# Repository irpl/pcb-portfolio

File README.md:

# PCB Design Portfolio

A selection of custom printed circuit boards I have designed and built, presented newest first. Each board was designed to solve a specific problem — a teaching platform, a weather station, and a remote water-quality monitor — rather than as a design exercise, and each one was fabricated and brought up in hardware.

---

## 1. ESP32 Sensor & Power Control Board

*Designed for the IoT course I teach at UWI.*

**Design files:** [KiCad schematic, layout, and project files →](https://github.com/irpl/ecse-simple-smart-hub-project-circuit)

This is the coursework platform board for the Internet of Things course I teach. It gives students a single board that covers the full loop of an IoT system: read the physical world, talk to a server, and act on the physical world in response.

An onboard **ESP32** reads a temperature sensor and a PIR motion sensor, and reports to a remote server. The server decides what should happen and instructs the ESP32, which then switches power through one of two **MOSFETs** to the corresponding output terminal. In other words, incoming power is routed to either of two loads under remote control — the two outputs are silkscreened `FAN` and `LIGHT`, which is the scenario students work through.

**Design notes**
- A landing footprint for an off-the-shelf **4.5–28 V** buck module (`J6`), so the board runs from any plain barrel-jack supply without designing a regulator onto it.
- Two low-side MOSFET switches (**IRLZ44N**, TO-220), each with a gate resistor. Logic-level parts were chosen deliberately: a standard MOSFET like the IRF-series needs several volts more than an ESP32's 3.3 V GPIO can supply to fully turn on, and would run hot in partial conduction. The IRLZ44N is fully enhanced from logic-level drive, so the ESP32 can switch real loads directly with no gate driver.
- Screw terminals for `TEMP`, `FAN` and `LIGHT`, a barrel jack for `POWER IN`, and a 3-pin header for the `PIR` — so students can wire and rewire the board without soldering.

The bare board and two populated builds are shown below — one with the ESP32 devkit soldered directly, and one built with female headers and a drop-in buck module so the ESP32 can be swapped out. Making the board survive a classroom full of students was as much a design constraint as the circuit itself.

<table>
  <tr>
    <th>Bare board</th>
    <th colspan="2">Assembled board</th>
  </tr>
  <tr>
    <td></td>
    <td></td>
    <td></td>
  </tr>
  <tr>
    <td></td>
    <td align="center"><sub>ESP32 soldered directly</sub></td>
    <td align="center"><sub>ESP32 on removable headers</sub></td>
  </tr>
</table>

---

## 2. Raspberry Pi Zero Weather Station HAT

**Design files:** [fab-ready Gerbers, plus a schematic and layout reconstructed from the copper →](https://github.com/irpl/pi-zero-weather-hat-circuit) &nbsp;•&nbsp; **Firmware:** [pi-weather →](https://github.com/irpl/pi-weather)

A custom HAT for the Raspberry Pi Zero, built to drive a weather station kit I had bought a few years earlier. Rather than leave the circuit on a breadboard or commit it to perfboard, I designed a proper HAT for it.

I started from a basic Pi Zero HAT footprint found on GitHub, which gave me only the board outline, the four mounting holes, and the GPIO header. **Everything else on the board is my own design.**

**Design notes**
- A footprint for a **BME280** breakout provides temperature and humidity (not fitted in the photos below).
- An **MCP3008** ADC reads the kit's resistive wind vane, since the Pi has no analogue inputs of its own.
- Two **RJ11/RJ12 jacks** bring in the kit's wind and rainfall sensors — silkscreened `Wind` and `RainFall` — so the outdoor sensors plug in with standard cable instead of flying leads.
- Sized and drilled to sit on the Pi Zero as a proper HAT, so the finished unit stays compact enough to deploy.

Laid out in **KiCad** as a two-layer board and fabricated in November 2020. The [design files](https://github.com/irpl/pi-zero-weather-hat-circuit) include the exact Gerber and drill set sent to the fab, so the board is reproducible as-is.

The original KiCad project for this board was lost. The schematic and layout in that repo were **reconstructed from the Gerbers** — the netlist recovered from the copper itself, then cross-checked against the firmware — and are clearly labelled as such.

| Bare boards (fab batch) | Assembled, seated on a Pi Zero | HAT and Pi Zero (exploded) |
|---|---|---|
|  |  |  |

---

## 3. Water Quality Sensor Interface Board

**Design files:** [Eagle schematic and layout →](https://github.com/irpl/water-quality-sensor-circuit) &nbsp;•&nbsp; **Server:** [watermon — the listener this board uploads to →](https://github.com/irpl/watermon)

The oldest board here, built to get readings off a water quality sensor and onto a server with no wired network anywhere nearby.

The sensor speaks **RS-232**, which a microcontroller cannot read directly. On this board an **Arduino Nano** sits behind a **MAX233** transceiver that converts the sensor's incoming RS-232 signals down to TTL serial the Nano can read. The Nano then pushes that data to a remote server over the cellular network using a **SIM800** module with an ordinary SIM and data plan.

**Design notes**
- **MAX233** rather than the more common MAX232: it integrates the charge-pump capacitors, so the RS-232 level shifter needs no external capacitors at all — fewer parts to place and fewer things to fail in the field.
- **DB9 connector** on the board edge so the sensor plugs straight in with a standard serial cable.
- Footprints for the Arduino Nano and the Adafruit **SIM800** cellular module, plus a 2×3 ICSP header.
- Screw terminal for field power.

This one is essentially a protocol-and-transport bridge: a legacy serial instrument on one end, a cellular uplink on the other, and level translation in between.

The board was laid out in **Eagle** as a two-layer design; the [schematic and layout](https://github.com/irpl/water-quality-sensor-circuit) are available separately.

| Bare board | Assembled |
|---|---|
|  |  |

---

## About

These boards span roughly seven years of design work, from the RS-232-to-cellular bridge through to the current teaching platform. Across all three the common thread is designing boards to be **built, deployed, and maintained** — screw terminals and standard connectors instead of flying leads, off-the-shelf modules on plain header footprints so a failed part can be swapped, and part choices (like the MAX233) that cut the component count down — rather than boards that only work on the bench.

Happy to discuss any of them in more detail, including schematics and layout.

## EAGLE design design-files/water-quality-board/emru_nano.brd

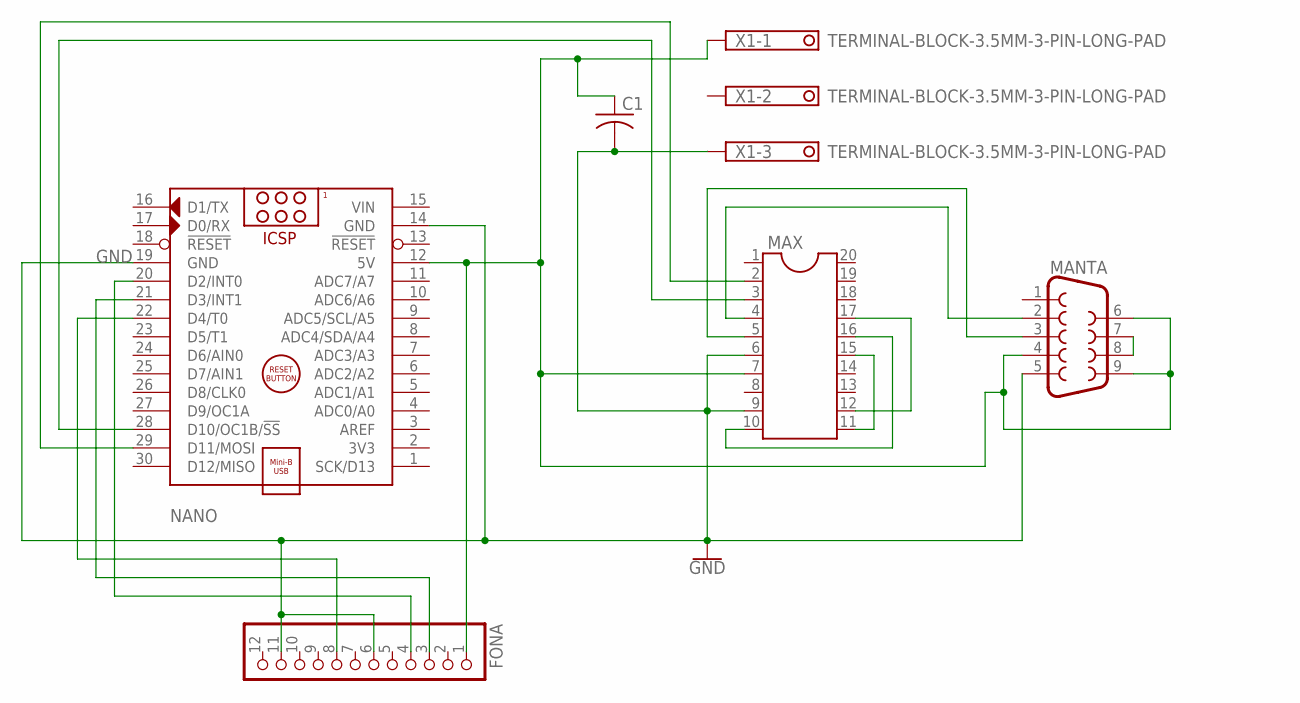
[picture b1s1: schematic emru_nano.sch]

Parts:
C1: C-US025-025X050; C025-025X050
FONA: PINHD-1X12; 1X12
MANTA: DB9MALE; DB9_MALE
MAX: DIL20
NANO: ARDUINO_NANO
X1: TERMINAL-BLOCK-3.5MM-3-PIN-LONG-PAD; TERMINAL-BLOCK-3-PIN-3.5MM-LONG-PAD

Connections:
GND: C1.2, FONA.6, FONA.11, MANTA.5, MAX.6, MAX.9, NANO.14 (GND), NANO.19 (GND), X1.3
unnamed: MANTA.7, MANTA.8
unnamed: FONA.4, NANO.20 (D2/INT0)
unnamed: C1.1, FONA.1, MANTA.4, MANTA.6, MANTA.9, MAX.7, NANO.12 (5V), X1.1
unnamed: MAX.10, MAX.16
unnamed: MAX.11, MAX.15
unnamed: MAX.12, MAX.17
unnamed: MANTA.2, MAX.4
unnamed: MANTA.3, MAX.5
unnamed: MAX.2, NANO.29 (D11/MOSI)
unnamed: MAX.3, NANO.28 (D10/OC1B/!SS)
unnamed: FONA.3, NANO.21 (D3/INT1)
unnamed: FONA.8, NANO.22 (D4/T0)
VIN: NANO.15 (VIN)

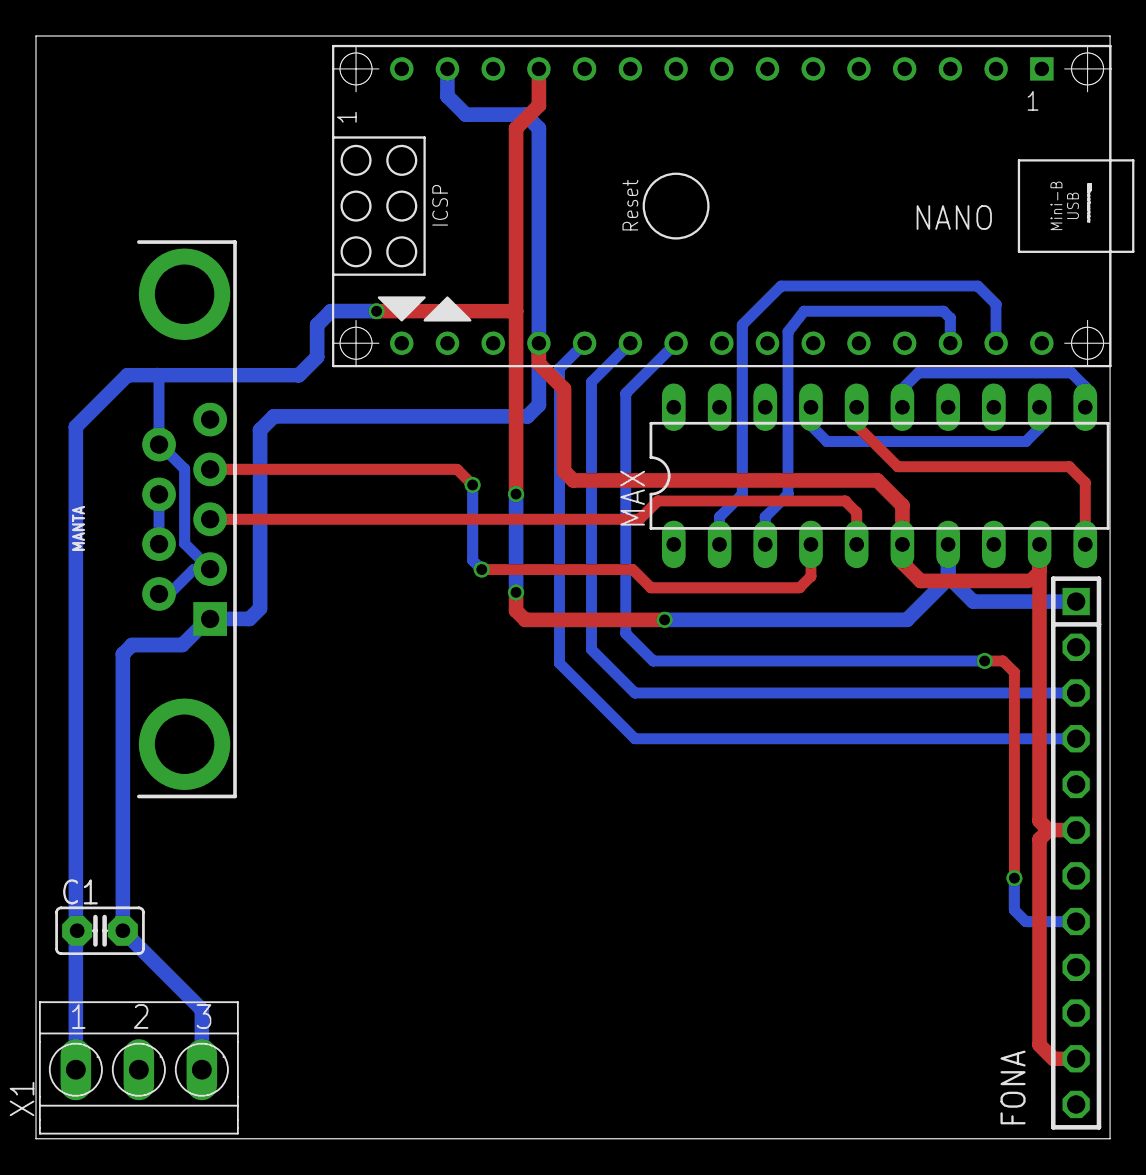
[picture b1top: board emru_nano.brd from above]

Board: 2 copper layers, 59.7 x 61.3 mm, 6 parts (0 on the bottom side), 13 nets.

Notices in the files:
parts and their libraries:
SparkFun-Connectors: Licensing: Creative Commons ShareAlike 4.0 International - https://creativecommons.org/licenses/by-sa/4.0
